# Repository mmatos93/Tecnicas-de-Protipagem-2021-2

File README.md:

# Tecnicas-de-Protipagem-2021-2

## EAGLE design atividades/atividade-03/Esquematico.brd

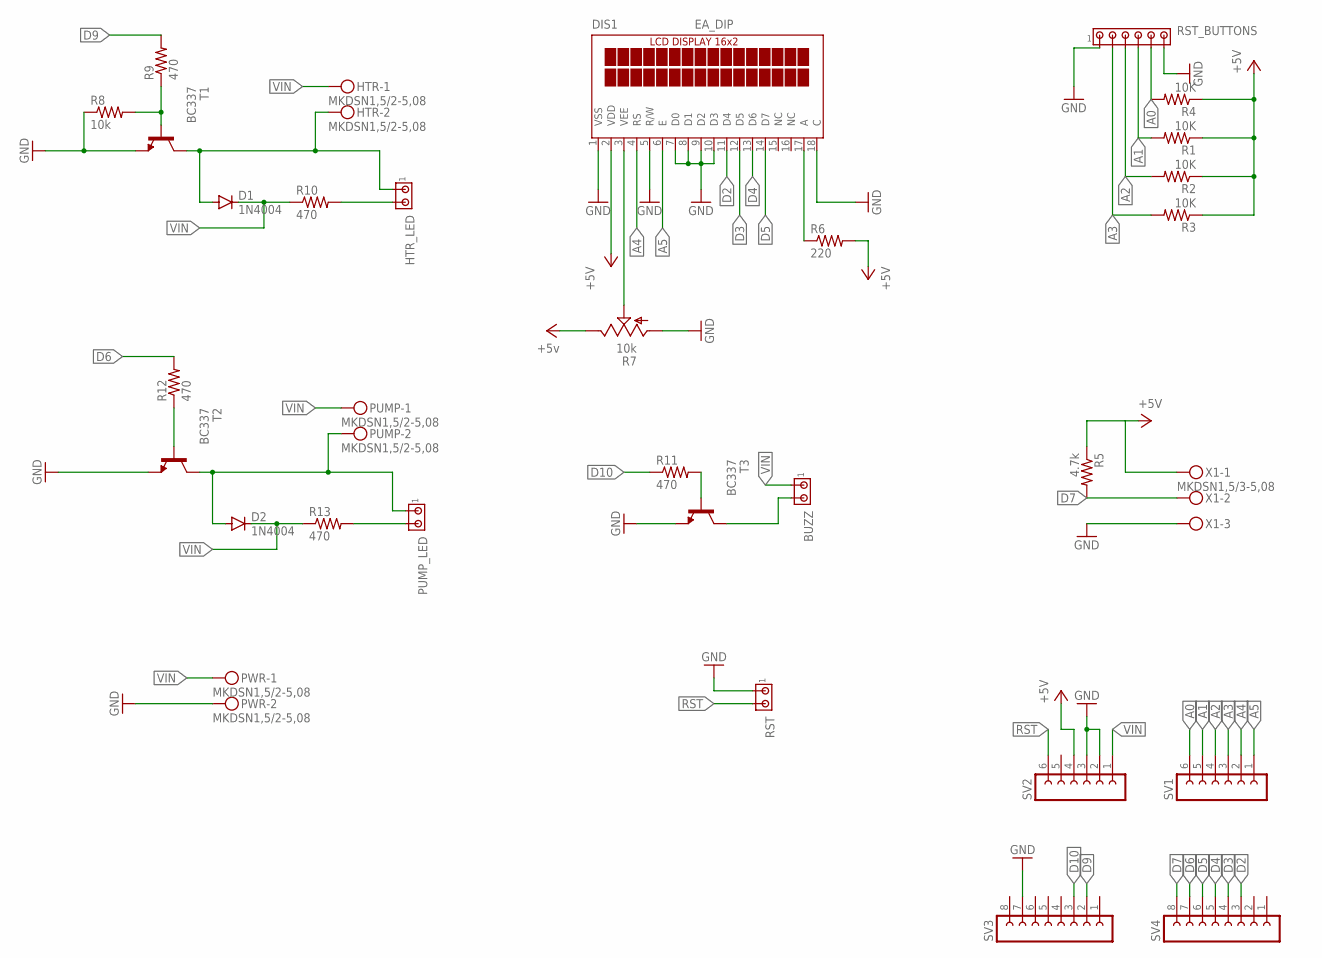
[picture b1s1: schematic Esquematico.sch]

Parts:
BUZZ: MTA02-100; 10X02MTA
D1, D2: 1N4004; DO41-10
DIS1: EA_DIP
HTR: MKDSN1,5/2-5,08
HTR_LED: MTA02-100; 10X02MTA
PUMP: MKDSN1,5/2-5,08
PUMP_LED: MTA02-100; 10X02MTA
PWR: MKDSN1,5/2-5,08
R1, R2, R3, R4: 10K; 0204/5
R5: 4.7k; 0204/5
R6: 220; 0204/5
R7: 10k; B25P
R8: 10k; 0204/5
R9, R10, R11, R12, R13: 470; 0204/5
RST: MTA02-100; 10X02MTA
RST_BUTTONS: MTA06-100; 10X06MTA
SV1, SV2: FE06-1; FE06
SV3, SV4: FE08-1; FE08
T1, T2, T3: BC337; TO92
X1: MKDSN1,5/3-5,08

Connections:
A0: R4.2, RST_BUTTONS.5, SV1.6
A1: R1.2, RST_BUTTONS.4, SV1.5
A2: R2.2, RST_BUTTONS.3, SV1.4
A3: R3.2, RST_BUTTONS.2, SV1.3
A4: DIS1.4 (RS), SV1.2
A5: DIS1.6 (E), SV1.1
D2: DIS1.11 (D4), SV4.3
D3: DIS1.12 (D5), SV4.4
D4: DIS1.13 (D6), SV4.5
D5: DIS1.14 (D7), SV4.6
D6: R12.2, SV4.7
D7: R5.2, SV4.8, X1.2
D9: R9.2, SV3.2
D10: R11.1, SV3.3
GND: DIS1.1 (VSS), DIS1.5 (R/W), DIS1.7 (D0), DIS1.8 (D1), DIS1.9 (D2), DIS1.10 (D3), DIS1.18 (C), PWR.2, R7.A, R8.1, RST.1, RST_BUTTONS.1, RST_BUTTONS.6, SV2.2, SV2.3, SV3.7, T1.1 (E), T2.1 (E), T3.1 (E), X1.3
unnamed: DIS1.3 (VEE), R7.S
unnamed: R12.1, T2.2 (B)
unnamed: R8.2, R9.1, T1.2 (B)
unnamed: DIS1.17 (A), R6.1
unnamed: D1.A, HTR.2, HTR_LED.1, T1.3 (C)
unnamed: HTR_LED.2, R10.2
unnamed: D2.A, PUMP.2, PUMP_LED.1, T2.3 (C)
unnamed: PUMP_LED.2, R13.2
unnamed: R11.2, T3.2 (B)
unnamed: BUZZ.2, T3.3 (C)
RST: RST.2, SV2.6
VCC: DIS1.2 (VDD), R1.1, R2.1, R3.1, R4.1, R5.1, R6.2, R7.E, SV2.4, X1.1
VIN: BUZZ.1, D1.C, D2.C, HTR.1, PUMP.1, PWR.1, R10.1, R13.1, SV2.1

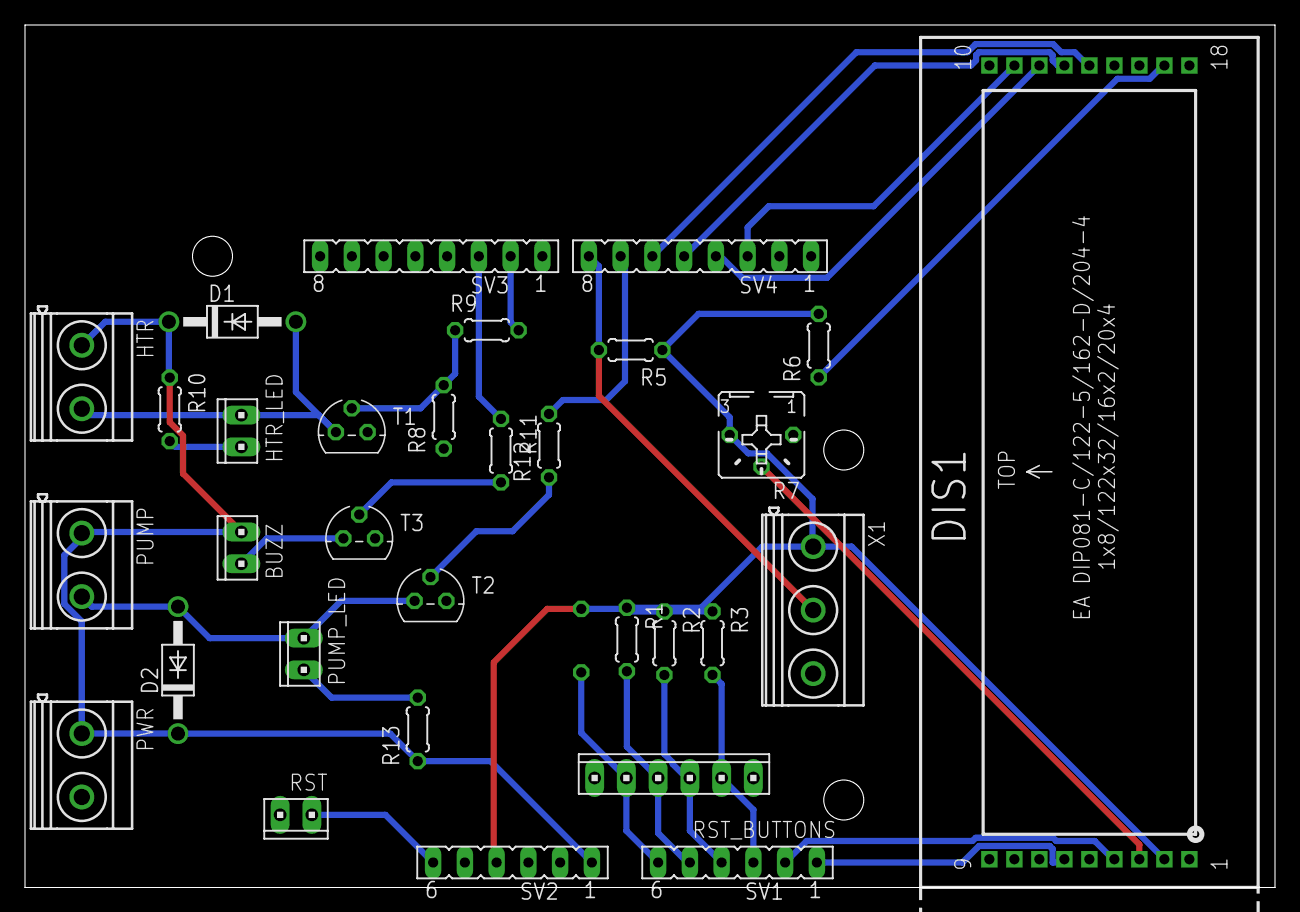
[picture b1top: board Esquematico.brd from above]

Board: 2 copper layers, 100.0 x 69.0 mm, 32 parts (1 on the bottom side), 28 nets.

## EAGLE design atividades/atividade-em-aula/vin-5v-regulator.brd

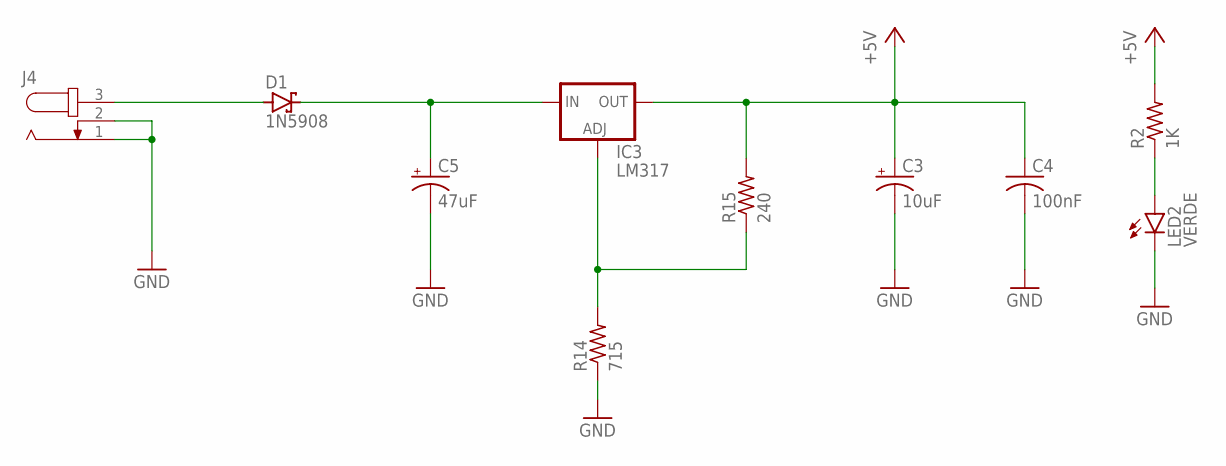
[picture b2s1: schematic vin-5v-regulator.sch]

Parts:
C3: 10uF; E2,5-6E
C4: 100nF; C025-030X050
C5: 47uF; E2,5-6E
D1: 1N5908; C4111-15
IC3: LM317; 317TS
J4: JACK-PLUG0; SPC4077
LED2: VERDE; LED5MM
R2: 1K; 0207/10
R14: 715; 0207/10
R15: 240; 0207/10

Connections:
+5V: C3.+, C4.1, IC3.2 (OUT), R2.2, R15.2
GND: C3.-, C4.2, C5.-, J4.1, J4.2, LED2.K (C), R14.1
unnamed: D1.A, J4.3
unnamed: C5.+, D1.C, IC3.3 (IN)
unnamed: IC3.1 (ADJ), R14.2, R15.1
unnamed: LED2.A, R2.1

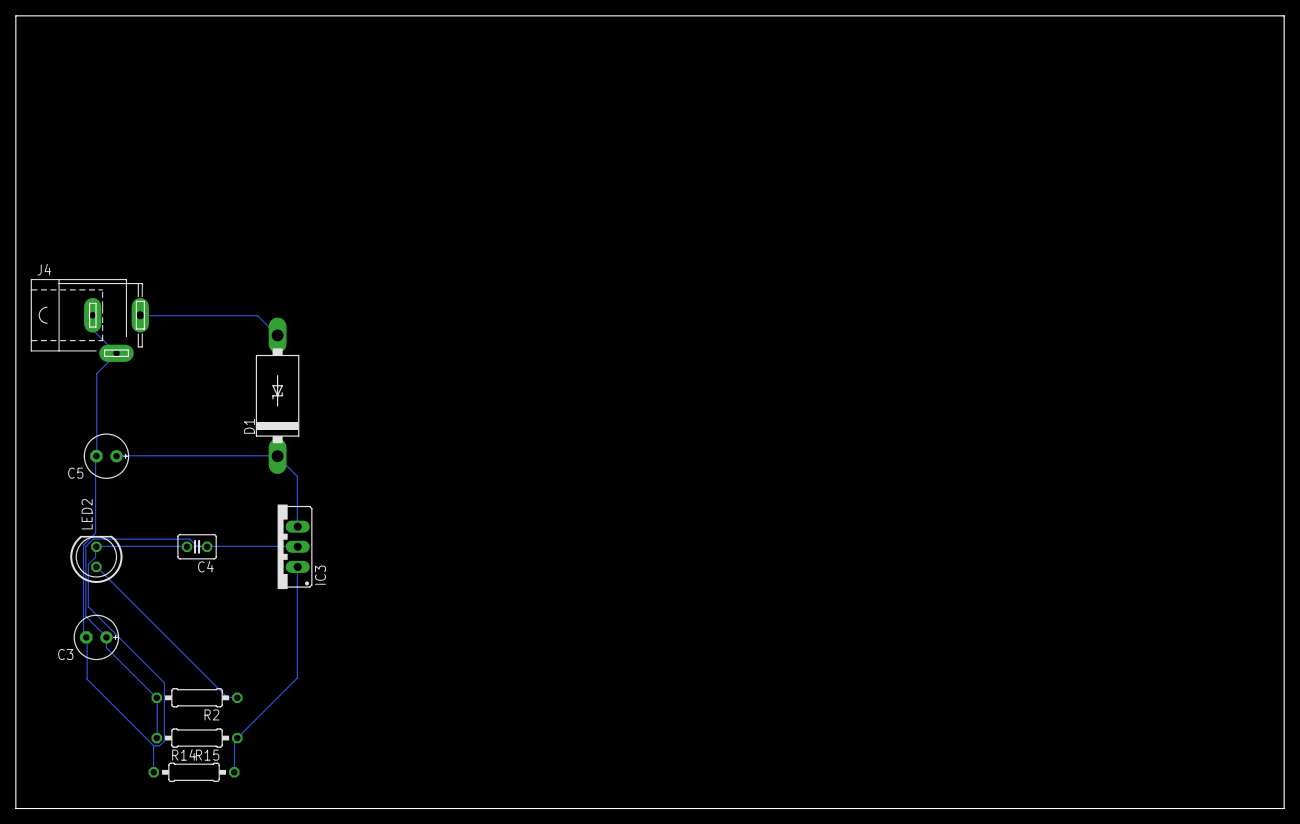
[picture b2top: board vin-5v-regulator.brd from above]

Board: 2 copper layers, 160.0 x 100.0 mm, 10 parts (0 on the bottom side), 6 nets.

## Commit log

2021-12-01 subindo o arquivo referente a segunda atividade da disciplina
2021-12-14 Atividade feita em aula
2021-12-14 Atividade em sala
2021-12-14 mover os arquivos para a pasta correta
2021-12-14 roteamento automatico
2021-12-14 atualizando a estrutura das pastas
2021-12-20 organizando as atividades nas pastas corretas
2021-12-24 Adiciona o arquivo de livraria com o display lcd 20x4
